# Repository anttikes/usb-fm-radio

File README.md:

# USB FM Radio

## Overview

This repository presents a USB FM Radio hardware device, consisting of the electronic schematic and PCB layout files drawn with KiCad, a C-language firmware implementation for an STM32 microcontroller and a GUI application for operating the radio device.

> [!IMPORTANT]
> This repository is still under heavy development, and quite many of the things are still unfinished.

Highlights:
 - The schematic consists of an STM32F042-based microcontroller, Si4705-D60 FM Radio Receiver, SG-3030CM crystal oscillator, a radio frontend and the supporting circuitry
 - The microcontroller controls the radio chip via an I2C interface, and receives digital audio from the tuner via an I2S interface
 - The firmware presents a USB 2.0 -compliant USB Audio device for the host computer, together with a Human Interface Device (HID) device for controlling the tuner chip
 - The GUI application allows the user to control the device, tune to a station, adjust volume, and other operations

## Prerequirements & Getting started

> [!IMPORTANT]
> This repository uses Git submodules. Use `git clone --recursive-submodules <url>` to clone everything in one go.
> 
>If you forgot to clone the submodule you can recover with the following commands:
> ```
> cd <local clone directory>
> git submodule update --init
> ```

The repository is structured around a "multi-root workspace" for Visual Studio Code. Thus, you will need VS Code, and you can install it from [here](https://code.visualstudio.com/Download). After installing, open the `usb-fm-radio.code-workspace` file from the root folder.

Both firmware and GUI portions have specific requirements regarding their build environment. Review the README.md files in each subdirectory for more details.

## Where to get an antenna?

In order to effectively receive radio broadcasts you will need an antenna. Any 50 Ohm matched antenna will do fine. I personally used [this antenna](https://www.amazon.com/POBADY-Sections-Telescopic-Connector-Replacement/dp/B09BVNK7WV?th=1) from Amazon

## Copyright & License

This repository consists of both original work by the author, and from work provided by third parties. 

The original work presented in this repository (the KiCad project & files, portions of firmware not originating from a third party, and the GUI application) are copyrighted to the owner of this repository. These portions are entirely licensed under the Creative Commons NonCommercial Sharealike license (CC-BY-NC-SA).

The implications of this license can be found in https://creativecommons.org/licenses/by-nc-sa/4.0/

All other work is copyrighted to their respective owners, and governed by licenses dictated by them. Review the Acknowledgements section for more details.

## Acknowledgements

This repository uses the following work from third parties:
 - Fonts from the DSEG7 series font family. Copyright, license terms and other information related to this font can be found from [keshikan/DSEG](https://github.com/keshikan/DSEG).
 - A forked version of librdsparser. Copyright, license terms and other information related to the library can be found from [kkonradpl/librdsparser](https://github.com/kkonradpl/librdsparser/).
 - A 3D model for the Bat Wireless Coaxial connector, courtesy of [Flux AI](https://www.flux.ai/lcsc/bwsma-ke-z001)

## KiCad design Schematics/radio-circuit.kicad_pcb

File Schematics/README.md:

# The schematic

This folder contains the KiCad schematic and PCB layout file for the board.

## Working on the project

To open this project download and install KiCad v10 for your operating system from [this page](https://www.kicad.org/download/).

## Generating the Bill of Materials

The KiCad project file contains a pre-made Bill of Materials definition preset that matches the format expected by JLCPCB. To generate a bill of materials for the project, open the schematic file, first choose "Tools" > "Generate Bill of Materials" and then switch to the "Edit" tab. From the preset selection in bottom-left choose "JLCPCB". Click "Apply, Save Schematic and Continue", and then "Export".

The Bill of Materials file (`radio-circuit.csv`) appears into the `output` folder.

## Generating Gerber, drill and component placement files

The KiCad project file contains the JLCPCB-compatible settings for Gerber and drill files. To generate them open the PCB Editor of the project, and:
 - Choose "File" > "Fabrciation Outputs" > "Gerbers" and "Plot" to generate the `.gbl` files to the `output` folder.
 - Choose "File" > "Fabrication Outputs" > "Drill Files" and "Generate" to generate the `.drl` files to the `output` folder.

Finally, choose "File" > "Fabrication Outputs" > "Component Placement", and click "Generate Position File" to generate the component placement file. The project uses top-side placement only so you can delete the `bottom-pos` file that appears.

### Modifying the component placement file

The file generated is not directly compatible with JLCPCB. You will have to edit the according to [these instructions](https://jlcpcb.com/help/article/How-to-generate-the-BOM-and-Centroid-file-from-KiCAD), from the "Generating Pick and Place files" onwards.

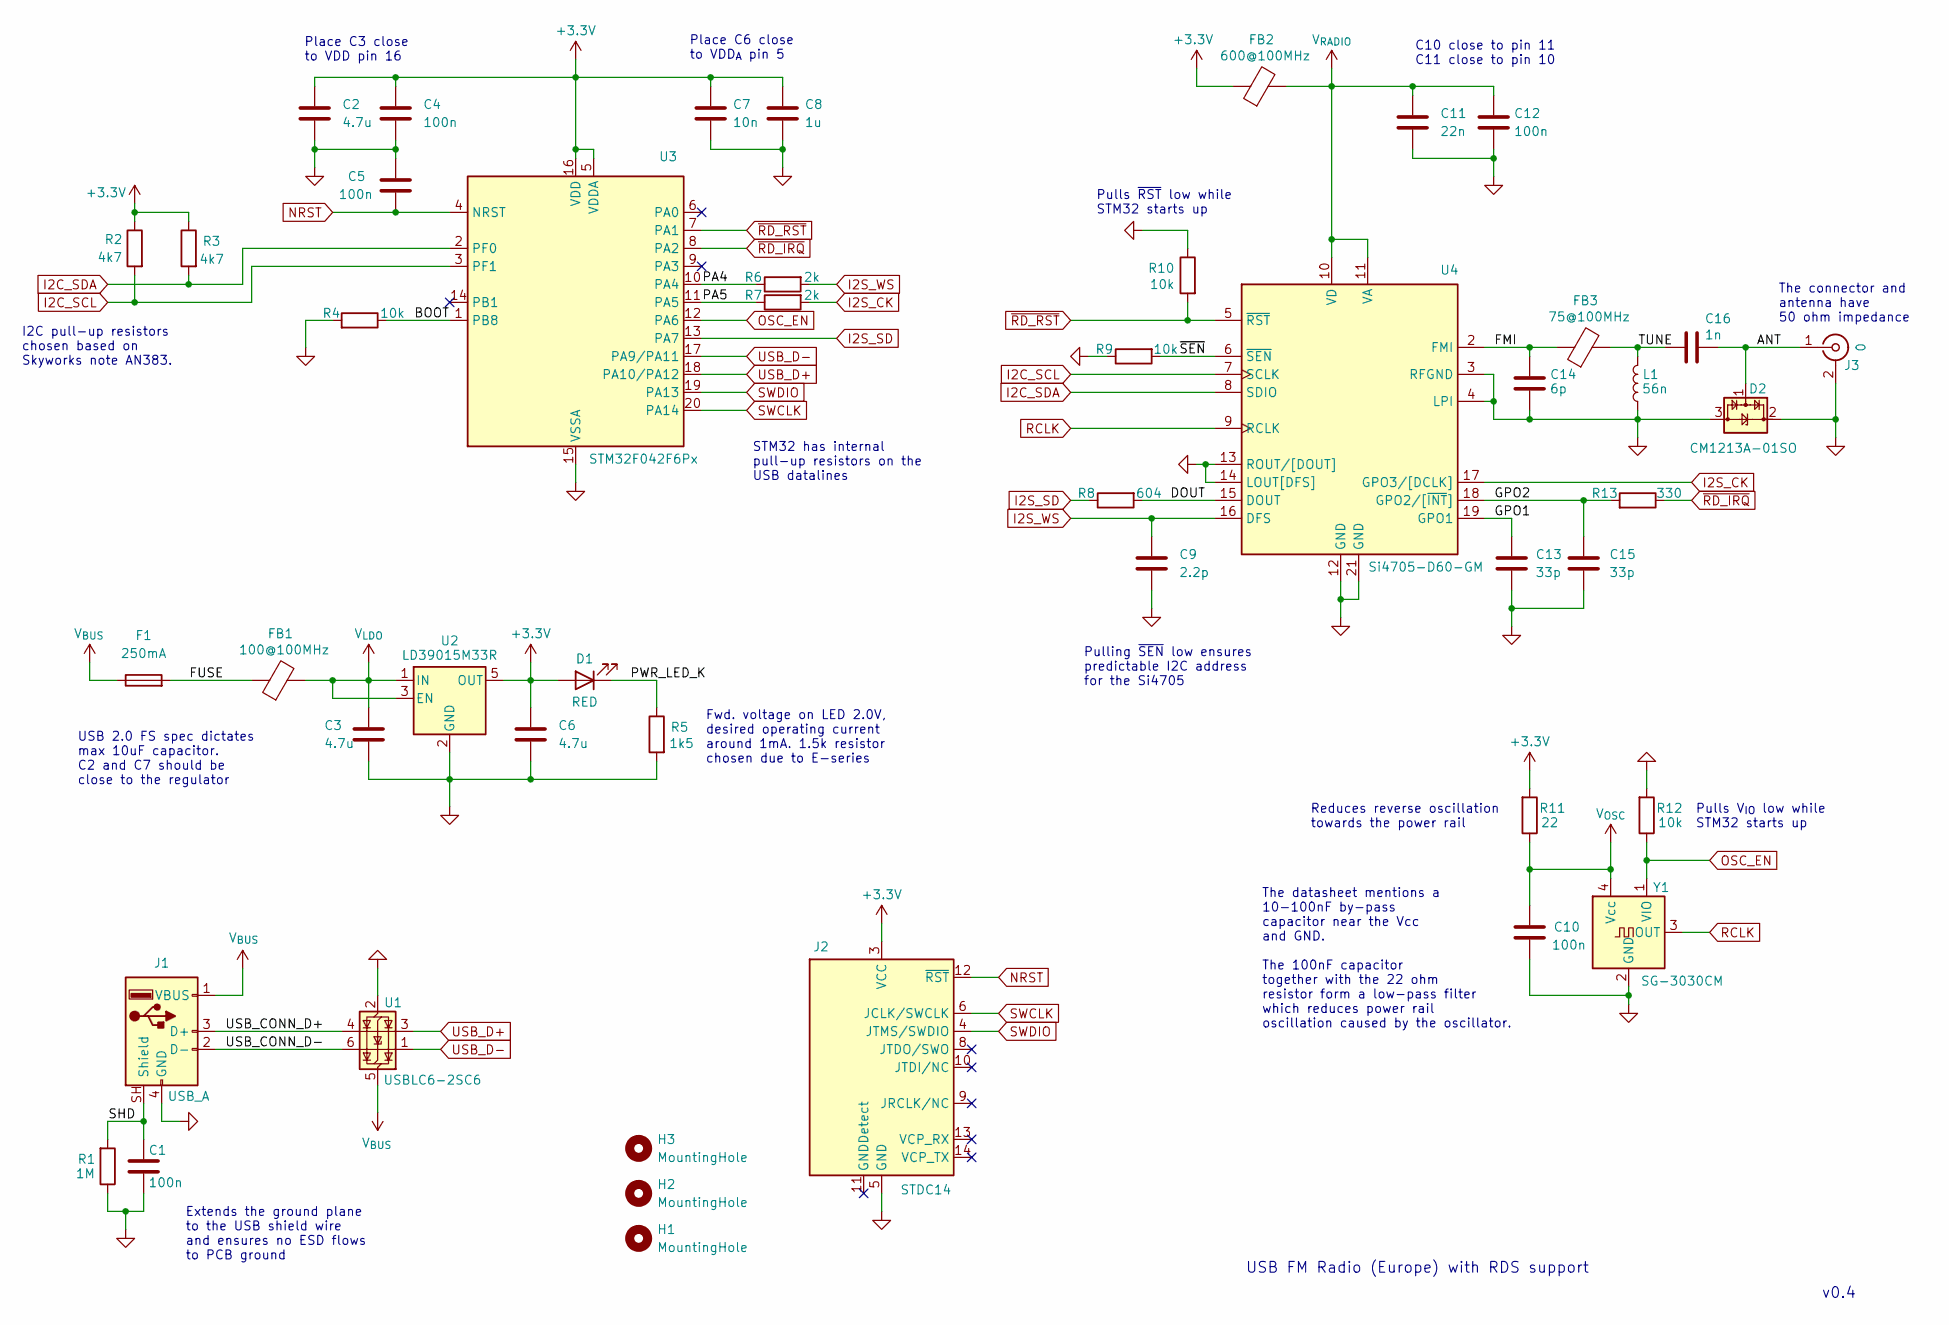
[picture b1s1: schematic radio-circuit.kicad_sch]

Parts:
C1: 100n; C_0805_2012Metric; JLCPCB Part Number C28233
C2, C3, C6: 4.7u; C_0603_1608Metric; JLCPCB Part Number C19666
C4, C5: 100n; C_0402_1005Metric; JLCPCB Part Number C1525
C7: 10n; C_0402_1005Metric; JLCPCB Part Number C15195
C8: 1u; C_0603_1608Metric; JLCPCB Part Number C15849
C9: 2.2p; C_0402_1005Metric; JLCPCB Part Number C1559
C10, C12: 100n; C_0402_1005Metric; JLCPCB Part Number C307331
C11: 22n; C_0402_1005Metric; JLCPCB Part Number C1532
C13, C15: 33p; C_0402_1005Metric; JLCPCB Part Number C1562
C14: 6p; C_0402_1005Metric; JLCPCB Part Number C30274
C16: 1n; C_0603_1608Metric; JLCPCB Part Number C1636
D1: RED; LED_0805_2012Metric; JLCPCB Part Number C84256
D2: CM1213A-01SO; SOT-23; JLCPCB Part Number C558429
F1: 250mA; Fuse_0603_1608Metric; JLCPCB Part Number C207012
FB1: 100@100MHz; L_0603_1608Metric; JLCPCB Part Number C14709
FB2: 600@100MHz; L_0402_1005Metric; JLCPCB Part Number C76886
FB3: 75@100MHz; L_0402_1005Metric; JLCPCB Part Number C113009
H1, H2, H3: MountingHole; MountingHole_JLCPCB
J1: USB_A; USB_A_AM180-01-T1-W; JLCPCB Part Number C19077262
J2: STDC14; PinHeader_2x07_P1.27mm_Vertical; JLCPCB Part Number C2935955
J3: 0; SMA_BAT_Wireless_BWSMA-KE-Z001; JLCPCB Part Number C496549
L1: 56n; L_0603_1608Metric; JLCPCB Part Number C98080
R1: 1M; R_0805_2012Metric; JLCPCB Part Number C17514
R2, R3: 4k7; R_0402_1005Metric; JLCPCB Part Number C25900
R4, R9, R10, R12: 10k; R_0402_1005Metric; JLCPCB Part Number C25744
R5: 1k5; R_0402_1005Metric; JLCPCB Part Number C25867
R6, R7: 2k; R_0402_1005Metric; JLCPCB Part Number C4109
R8: 604; R_0402_1005Metric; JLCPCB Part Number C8369
R11: 22; R_0402_1005Metric; JLCPCB Part Number C25092
R13: 330; R_0402_1005Metric; JLCPCB Part Number C25104
U1: USBLC6-2SC6; SOT-23-6; JLCPCB Part Number C7519
U2: LD39015M33R; SOT-23-5; JLCPCB Part Number C2798212
U3: STM32F042F6Px; TSSOP-20_4.4x6.5mm_P0.65mm; JLCPCB Part Number C81000
U4: Si4705-D60-GM; Skyworks_QFN-20-1EP_3x3mm_P0.5mm_EP1.8x1.8mm; JLCPCB Part Number C1526114
Y1: SG-3030CM; Oscillator_SMD_SeikoEpson_SG3030CM; JLCPCB Part Number C256005

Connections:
+3.3V: C2.1, C4.1, C6.1, C7.1, C8.1, D1.2 (A), FB2.1, J2.3 (VCC), R2.1, R3.1, R11.2, U2.5 (OUT), U3.5 (VDDA), U3.16 (VDD)
/ ~SEN: R9.2, U4.6 (~SEN)
/ANT: C16.1, D2.1 (CH1), J3.1 (In)
/BOOT: R4.1, U3.1 (PB8)
/DOUT: R8.2, U4.15 (DOUT)
/FMI: C14.1, FB3.1, U4.2 (FMI)
/FUSE: F1.2, FB1.1
/GPO1: C13.1, U4.19 (GPO1)
/GPO2: C15.1, R13.2, U4.18 (GPO2/[~INT])
/PA4: R6.1, U3.10 (PA4)
/PA5: R7.1, U3.11 (PA5)
/PWR_LED_K: D1.1 (K), R5.1
/SHD: C1.2, J1.SH (Shield), R1.2
/TUNE: C16.2, FB3.2, L1.2
/USB_CONN_D+: J1.3 (D+), U1.4 (I/O2)
/USB_CONN_D-: J1.2 (D-), U1.6 (I/O1)
GND: C1.1, C2.2, C3.2, C4.2, C5.2, C6.2, C7.2, C8.2, C9.2, C10.2, C11.2, C12.2, C13.2, C14.2, C15.2, D2.2 (VP), D2.3 (VN), J1.4 (GND), J2.5 (GND), J2.7 (GND), J3.2 (Ext), L1.1, R1.1, R4.2, R5.2, R9.1, R10.1, R12.2, U1.2 (GND), U2.2 (GND), U3.15 (VSSA), U4.3 (RFGND), U4.4 (LPI), U4.12 (GND), U4.13 (ROUT/[DOUT]), U4.14 (LOUT[DFS]), U4.21 (GND), Y1.2 (GND)
I2C_SCL: R2.2, U3.3 (PF1), U4.7 (SCLK)
I2C_SDA: R3.2, U3.2 (PF0), U4.8 (SDIO)
I2S_CK: R7.2, U4.17 (GPO3/[DCLK])
I2S_SD: R8.1, U3.13 (PA7)
I2S_WS: C9.1, R6.2, U4.16 (DFS)
NRST: C5.1, J2.12 (~RST), U3.4 (NRST)
OSC_EN: R12.1, U3.12 (PA6), Y1.1 (VIO)
RCLK: U4.9 (RCLK), Y1.3 (OUT)
SWCLK: J2.6 (JCLK/SWCLK), U3.20 (PA14)
SWDIO: J2.4 (JTMS/SWDIO), U3.19 (PA13)
USB_D+: U1.3 (I/O2), U3.18 (PA10/PA12)
USB_D-: U1.1 (I/O1), U3.17 (PA9/PA11)
V_{BUS}: F1.1, J1.1 (VBUS), U1.5 (VBUS)
V_{LDO}: C3.1, FB1.2, U2.1 (IN), U2.3 (EN)
V_{OSC}: C10.1, R11.1, Y1.4 (Vcc)
V_{RADIO}: C11.1, C12.1, FB2.2, U4.10 (VD), U4.11 (VA)
~RD_IRQ: R13.1, U3.8 (PA2)
~RD_RST: R10.2, U3.7 (PA1), U4.5 (~RST)

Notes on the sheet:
Pulls ~{RST} low while STM32 starts up
Place C6 close to VDD_{A} pin 5
USB FM Radio (Europe) with RDS support
STM32 has internal pull-up resistors on the USB datalines
I2C pull-up resistors chosen based on Skyworks note AN383.
USB 2.0 FS spec dictates max 10uF capacitor. C2 and C7 should be close to the regulator
The connector and antenna have 50 ohm impedance
Extends the ground plane to the USB shield wire and ensures no ESD flows to PCB ground
C10 close to pin 11 C11 close to pin 10
Pulls V_{IO} low while STM32 starts up
Reduces reverse oscillation towards the power rail
v0.4
Pulling ~{SEN} low ensures predictable I2C address for the Si4705
Fwd. voltage on LED 2.0V, desired operating current around 1mA. 1.5k resistor chosen due to E-series
The datasheet mentions a 10-100nF by-pass capacitor near the Vcc and GND. The 100nF capacitor together with the 22 ohm resistor form a low-pass filter which reduces power rail oscillation caused by the oscillator.
Place C3 close to VDD pin 16

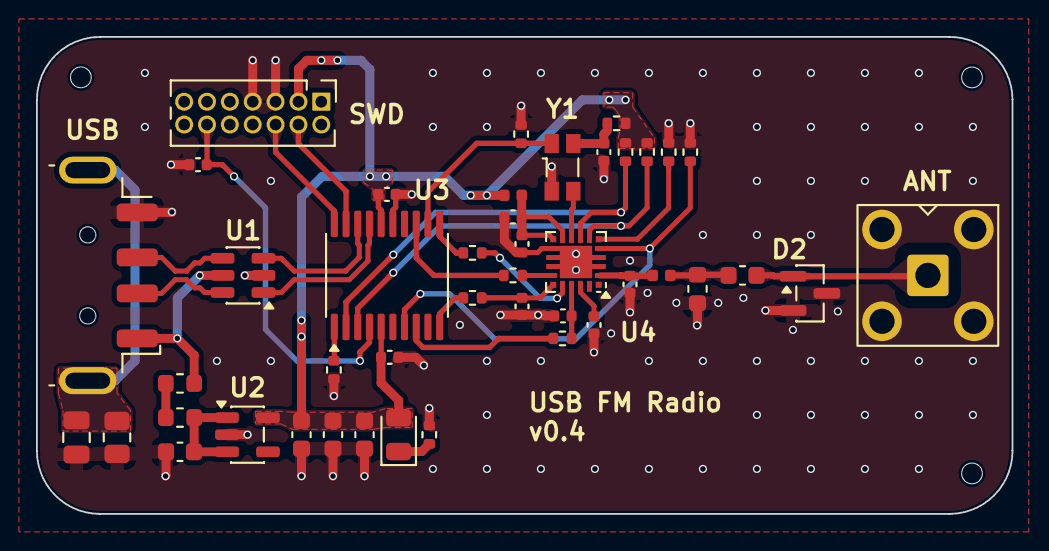
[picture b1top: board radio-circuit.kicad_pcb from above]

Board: 4 copper layers, 54.2 x 26.5 mm, 47 parts (0 on the bottom side), 35 nets.

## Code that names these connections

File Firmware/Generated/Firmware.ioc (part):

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Mcu.Name=STM32F042F6Px
Mcu.Package=TSSOP20
Mcu.UserName=STM32F042F6Px
PA1.GPIOParameters=GPIO_Label
PA1.GPIO_Label=RD_RST
PA1.Signal=GPIO_Output
PA11.Mode=Device
PA11.Signal=USB_DM
PA12.Mode=Device
PA12.Signal=USB_DP
PA13.Mode=Serial_Wire
PA13.Signal=SYS_SWDIO
PA14.Mode=Serial_Wire
PA14.Signal=SYS_SWCLK
PA2.GPIOParameters=GPIO_Label,GPIO_ModeDefaultEXTI
PA2.GPIO_Label=RD_IRQ
PA2.GPIO_ModeDefaultEXTI=GPIO_MODE_IT_FALLING
PA2.Signal=GPXTI2
PA4.Mode=Half_Duplex_Master
PA4.Signal=I2S1_WS
PA5.Mode=Half_Duplex_Master
PA5.Signal=I2S1_CK
PA6.GPIOParameters=GPIO_Label
PA6.GPIO_Label=OSC_EN
PA6.Signal=GPIO_Output
PA7.Mode=Half_Duplex_Master
PA7.Signal=I2S1_SD
PF0-OSC_IN.Mode=I2C
PF0-OSC_IN.Signal=I2C1_SDA
PF1-OSC_OUT.Mode=I2C
PF1-OSC_OUT.Signal=I2C1_SCL
RCC.SYSCLKFreq_VALUE=38400000
RCC.SYSCLKSource=RCC_SYSCLKSOURCE_PLLCLK
board=custom

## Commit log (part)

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2025-09-28 Added initial readme
2025-09-28 Added license
2025-09-28 Added v0.1 schematic
2025-09-28 Added deprecation warning on v0.1
2025-09-28 Added v0.2 schematic, removed deprecation
2025-09-28 Added v0.2 bill of materials and position file
2025-09-28 Clarified copyright and licensing rules of the repo
2025-09-28 Initial firmware version
2025-09-28 Added Device Configuration Tool perspective
2025-09-28 Added IoC files
2025-09-28 Removed Eclipse metadata
2025-09-28 Disabled USBD debug as there's no printf
2025-09-28 Disabled backup from IoC
2025-09-28 Volume, mute and sampling frequency settings are now stored
2025-10-02 Updated readme & license
2025-10-03 Updated I2S to 48 kHz and adjusted clock settings to find a match
2025-10-05 Added low-level driver file & settings
2025-10-05 Added low-level initialization code
2025-10-05 Renamed all 'audio' variables to 'radio'
2025-10-05 Forgot to rename the ones in 'main.c'
2025-10-05 Removed temporary file
2025-10-05 Moved to use full HAL again
2025-10-07 Added submodules
2025-10-07 Removed 'Drivers' folder
2025-10-07 Moved USB tidbits to new folders
2025-10-07 Fixed project file
2025-10-07 Updated submodules to proper versions
2025-10-07 Updated copyright and license statements in original work
2025-10-07 Added note about submodules
2025-10-09 Added tinyusb submodule
2025-10-11 Removed STM32 USB library
2025-10-12 Implemented basic TinyUSB version with 44 kHz sampling
2025-10-13 Switched to 48 kHz sampling
2025-10-21 Added HID interface and callbacks
2025-10-21 Updated TinyUSB to 0.19.0
2025-10-21 Switched to GCC 18, enabled pedantic warnings
2025-10-25 Added timer initialization for status updates
2025-11-08 Updated project settings
2025-11-08 Fixed USB peripheral clock start location
2025-11-08 Removed STM32CubeIDE files
2025-11-08 Added hand-crafted CMake files to make it work
2025-11-09 Removed project bundles
2025-11-09 Added launch.json for debugging
2025-11-09 Adjusted compilation flags to produce smaller debug build
2025-11-09 Added necessary bundles for STM32Cube extension
2025-11-09 Added recommended extensions
2025-11-09 Removed independent submodules and switched to STM32CubeF0
2025-11-09 Fixed project config, added GDB bundle
2025-11-09 TinyUSB is now included in main project, and not a library
2025-11-09 Moved radio module outside of "Core"
2025-11-09 Added .mxproject file
2025-11-09 Switched to new startup file
2025-11-09 Switched to new linker script
2025-11-09 Moved IoC file to a subdirectory so code generation doesn't break stuff
2025-11-09 TinyUSB sources are now more independent
2025-11-12 Added clang-format
2025-11-12 Formatted header files and removed "user code"
2025-11-12 Adjusted formatting settings
2025-11-12 Upgraded STM32CubeF0 firmware
2025-11-12 Formatted source files
2025-11-12 Another formatting pass for headers
2025-11-15 Upgraded TinyUSB
2025-11-15 Removed extra formatting settings
2025-11-15 Formatted USB-related files
2025-11-15 Fixed file formatting
2025-11-20 Refactoring radio module
2025-11-20 Implemented interrupt-based approach for commands which do not return anything
2025-11-22 Removed unused file
2025-11-22 Implemented basic queue system for the radio commands
2025-11-22 Added commands for GPIO control
2025-11-22 Added Copilot instructions
2025-11-22 Changed all commands to use enqueuing mode
2025-11-22 Fixed docs, and added prelim support for receiving responses
2025-11-22 Parameter name harmonization
2025-11-23 Documentation updates; periodic RSQ updates
2025-11-23 Added state transition for "no output"
2025-11-23 Renamed command queue
2025-11-23 Support for non-command interrupts
2025-11-23 Added timer start for RSQ updates
2025-11-23 Enabled HID and sending of RSQ reports to host
2025-11-29 Moved timer startup to after tune completes
2025-11-29 RSQ is now sent also when tuned to station
2025-11-29 Added missing flags to GPIO control
2025-11-29 USB report and response retrieval are now done from the main loop
2025-11-29 Updated tinyusb and CubeF0
2025-12-05 Updated CubeF0
2025-12-06 Adjusted CMake settings
2025-12-06 Added missing configureArg
2025-12-06 Removed sub-project
2025-12-06 Install necessary bundles
2025-12-06 Switch the toolchain
2025-12-08 Remoted starm-clang toolchain
2025-12-08 Added cmake preset for MinGW & GUI
2025-12-08 Added simple GUI skeleton
2025-12-09 Added few Qt-related settings to CMakePresets
2025-12-09 Removed schematic & GUI
2025-12-09 Migrated firmware to the root
2025-12-09 Migrated remainin files
2025-12-09 Clean-up
2025-12-09 Re-enabled "cmake.configureArgs"
2025-12-09 Added submodule initialization script
2025-12-09 Fixed linker script location
2025-12-16 Moved STM32 extension settings files to "Firmware"
2025-12-16 Adjusted Firmware CMake files and toolchain
2025-12-16 Commented out environment printing
2025-12-17 Removed GUI stuff from CMakePresets
2025-12-17 Fixed Firmware settings
2025-12-17 Fixed GUI settings & CMake
2025-12-17 Addde workspace file
2025-12-17 Added extensions.json to Firmware
2025-12-17 Removed mingw compiler settings
2025-12-17 Added .qmlls.ini to .gitignore
2025-12-17 Added GUI extensions
2025-12-18 Removed STM32 bundles from GUI
2025-12-18 Fixed firmware build
2025-12-18 Moved clang-format
2025-12-18 Added tidbits for GUI build
2025-12-18 Fixed firmware output folder
2025-12-18 Added clangd
2025-12-18 Fixed firmware clangd
2025-12-18 Removed starm-clangd
2025-12-20 Adjusted GUI build to use Qt tools
2025-12-20 Enable format on save
2025-12-20 Tool C++ extension into use
2025-12-20 Removed unused cache variable from GUI
2025-12-20 GUI file formatting
2025-12-21 Fixed finding of CMake in GUI
2025-12-21 Added better debugging support for GUI
2025-12-21 Removed CMakePresets from GUI
2025-12-22 Added missing CMake and Ninja installation from STM32 extension
2025-12-22 Added missing bits from firmware's STM32 settings
2025-12-22 Removed STM32 bits from GUI
2025-12-22 Updated GUI instructions & workspace settings
2025-12-22 Re-enabled app launch from status bar
2025-12-22 Added basic main window styling & behavior
2025-12-22 Reorganized GUI files a bit
2025-12-26 Fixed debug settings in the GUI
2025-12-26 Added frequency control, LCD display and fonts
2025-12-26 Tune up & down buttons
2025-12-26 RDS information pane
2025-12-28 Fixes to radius and pane border colors
2025-12-29 Added signal strenght & noise ratio indicators
2025-12-30 Added power button & stereo indicator
2025-12-30 Fixed moden button's colors
2025-12-31 Made title bar an item instead of rectangle
2026-01-04 Some layout fixes
2026-01-06 Added hidapi as a GUI submodule
2026-01-06 Updated readme files
2026-01-06 Added some initial hidapi wirings
2026-01-06 Removed unused function declaration
2026-01-06 RSQ timer now resets the queue if it gets stuck
2026-01-08 Rename tuner control
2026-01-08 Added auto-generated clangd file, fixed settings
2026-01-08 Renamed GUI executable
2026-01-10 Removed tuner control
2026-01-10 Removed QML trace from debug output
2026-01-11 Increased the frequency of the RSQ timer
2026-01-11 Timer now stops on power-down, and starts also after seek completes
2026-01-11 Added a task for flashing the current binary into the MCU
2026-01-14 Relocated firmware source files
2026-01-17 When radio is tuned, use TuneStatus instead of RSQ
2026-01-17 Changed timer to use RSQ status since it is measured each time
2026-01-17 Added support for device listing, selection and showing signal quality
2026-01-17 Added screenshot of the current main window
2026-01-19 Disable controls if no device is selected
2026-01-19 Moved device enumeration to a thread pool worker
2026-01-19 Fixed an issue where device disconnection did not clear the pointer
2026-01-23 Switched to gnu2x standard
2026-01-23 Fixed parameter naming in timer init
2026-01-23 Moved timer callback to proper location
2026-01-23 Fixed alignments in descriptor file
2026-01-23 Moved report polling to a thread pool worker
2026-01-23 Configure FM de-emphasis to match Europe
2026-01-28 Generated agent instructions for both projects
2026-01-29 Refined firmware instructions
2026-01-29 Added missing instructions section
2026-01-31 Added "tune in progress" state for the radio
2026-02-05 Updated to use MSVC tools instead of MinGW
2026-02-05 Fixed .gitignore of the Generated folder
2026-02-05 Switched RSQ status to use TIM16, and enabled TIM17 for future use
2026-02-05 Fixed license texts, copyrights and CMake
2026-02-05 Store current frequency and report it to the GUI
2026-02-05 Added support for showing the frequency reading on UI
2026-02-06 ReportWorker can now read multiple simultaneous reports
2026-02-12 Added tuner dial pin
2026-02-12 Updated hidapi
2026-02-16 Refactored GUI to use the modern QML modules approach
2026-02-22 USB vendor and product ID now come from a header file
2026-02-22 USB Audio volume and mute now go all the way to the radio
2026-02-22 Flash task now always builds the firmware
2026-02-22 Rotated the MCU pins in the STM32CubeMX
2026-02-22 Adjusted audio and TinyUSB buffer sizes
2026-02-24 Refactored radio module to have dedicated property helpers, reducing bloat in common.h
2026-02-26 Renamed GUI's CMake project
2026-02-26 Generate a header-package as part of the firmware build
2026-02-28 Disabled waiting for the QML debugger to attach
2026-02-28 Moved CMakeLists.txt of the shared headers to the subdirectory
2026-02-28 Firmware now uses the shared structures, and GUI can react to them properly
2026-03-01 Preliminary support for seek up and down
2026-03-02 Firmware now reports command and report queue sizes in status report
2026-03-02 RSQStatus is now queried whenever device is in power up state
2026-03-02 ReportWorker can now signal DeviceManager to reset the current device if it errors out
2026-03-09 Added vertical antenna connector library
2026-03-09 Added schematic readme, PCB layout and 3D rendering
2026-03-14 Ignore the output folder in Schematic
2026-03-14 Upgraded STM32 tools to latest
2026-03-14 Added instructions for generating fabrication outputs
2026-03-14 Renamed symbol library
2026-03-14 Renamed footprint library
2026-03-14 Included 3D model for the coaxial connector
2026-04-10 Added I2C error callback to radio
2026-04-10 Added property setter for radio chip's REFCLK
2026-04-11 Removed unnecessary GPIO2 flag from the GPIOCtl call
2026-04-11 Switched I2C to fast mode
2026-04-11 Upgrade STM32CubeF0 to v1.11.6
2026-04-14 Fixed a broken symbol link in the schematic file
2026-04-21 Removed unused variable for HID callbacks
2026-04-21 Added Get Property report
2026-04-21 Removed unused code block
2026-04-21 Increased command queue capacity to 20
2026-04-21 Added properties for RDS settings
2026-04-21 Firmware now enables RDS processor
2026-04-21 First tune status after seek/tune now clears the STCINT bit
2026-04-23 Fix comment formatting in USB-related files
2026-04-23 Add librdsparser as submodule
2026-04-25 Aligned the C and C++ standard versions between projects
2026-04-25 Report members are now public in C++ side
2026-05-01 Migrated to KiCad v10 format
2026-05-01 Updated footprints and symbols to newest versions
2026-05-30 Fixed comments in the header file
2026-05-30 Fixed the race condition between interrupts, and the queue no longer overflows
2026-05-31 TinyUSB is now built as an optimized static library
2026-05-31 Added command for obtaining RDS status from the device
2026-05-31 Added registration of librdsparser callbacks, and an RDS processing forwarder
2026-05-31 Fixed rebase mishap
2026-05-31 The device now forwards RDS data to the library
2026-05-31 Fixed compile flag mismatch between firmware and librdsparser
2026-05-31 The device now reads RDS data when interrupt bits indicate its available
2026-06-02 Added function to reset RDS parser state
2026-06-02 Removed unused flag
2026-06-05 Update librdsparser to use the one with changed callbacks
2026-06-05 Add support for RDS reports
2026-06-06 HID report max packet size is now separate from the TinyUSB buffers
2026-06-06 Reduced number for FIFO buffers, and increased report buffer size
2026-06-06 Removed RDS stability counters
2026-06-06 RDS panel now resets after seek
2026-06-06 ReportWorker now supports RDS reports
